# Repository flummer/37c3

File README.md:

# 37c3 NFC Badge by Thomas Flummer

This is a simple badge, to play a little with NFC using the NXP NTAG I2C Plus chip. There is a PCB antenna coil for the RF interface (can eg. be used for communication with an NFC enabled phone), and there is a StemmaQT/Qwiic compatible connector for I2C communication, often found on many development boards or more advanced badges.

The onboard memory on the NTAG I2C Plus chip is 1K and can hold different data. The badges are preformated for NDEF records and there is a link record on there that includes a link to this repository, but you can change the content, eg. with the NXP TagWriter app for Android or iOS. Be aware that iOS needs the memory to be formatted as NDEF.

You can protect different sections and it is also possible via registers to protect write access to either RF/I2C or BOTH.

**WARNING** If you block access to both interfaces, you will **NOT** be able to change the content on the badge any more.

This badge is heavily inspired with pretty much all the electronics copied from the [BornHack 2023 badge](https://github.com/bornhack/badge2023/) with almosts the same features, though a little bit less memory (the BornHack 2023 version has 2K).

## Designed in KiCad v7

To open the project, you will need to install a recent release version or one of the nightly builds, KiCad v5 or v6 won't open this design.

Main Component:

- [NXP NT3H2111W0FHKH - NTAG I2C plus 1K, NFC Forum Type 2 Tag with I2C interface](https://www.nxp.com/part/NT3H2111W0FHK#/)
    - [datasheet](https://www.nxp.com/docs/en/data-sheet/NT3H2111_2211.pdf)

## License

The hardware design of the `main` branch of this repository is released under the following license:

* the "Creative Commons Attribution-ShareAlike 4.0 International License"
  (CC BY-SA 4.0) full text of this license is included in the LICENSE file
  and a copy can also be found at
  [http://creativecommons.org/licenses/by-sa/4.0/](http://creativecommons.org/licenses/by-sa/4.0/)

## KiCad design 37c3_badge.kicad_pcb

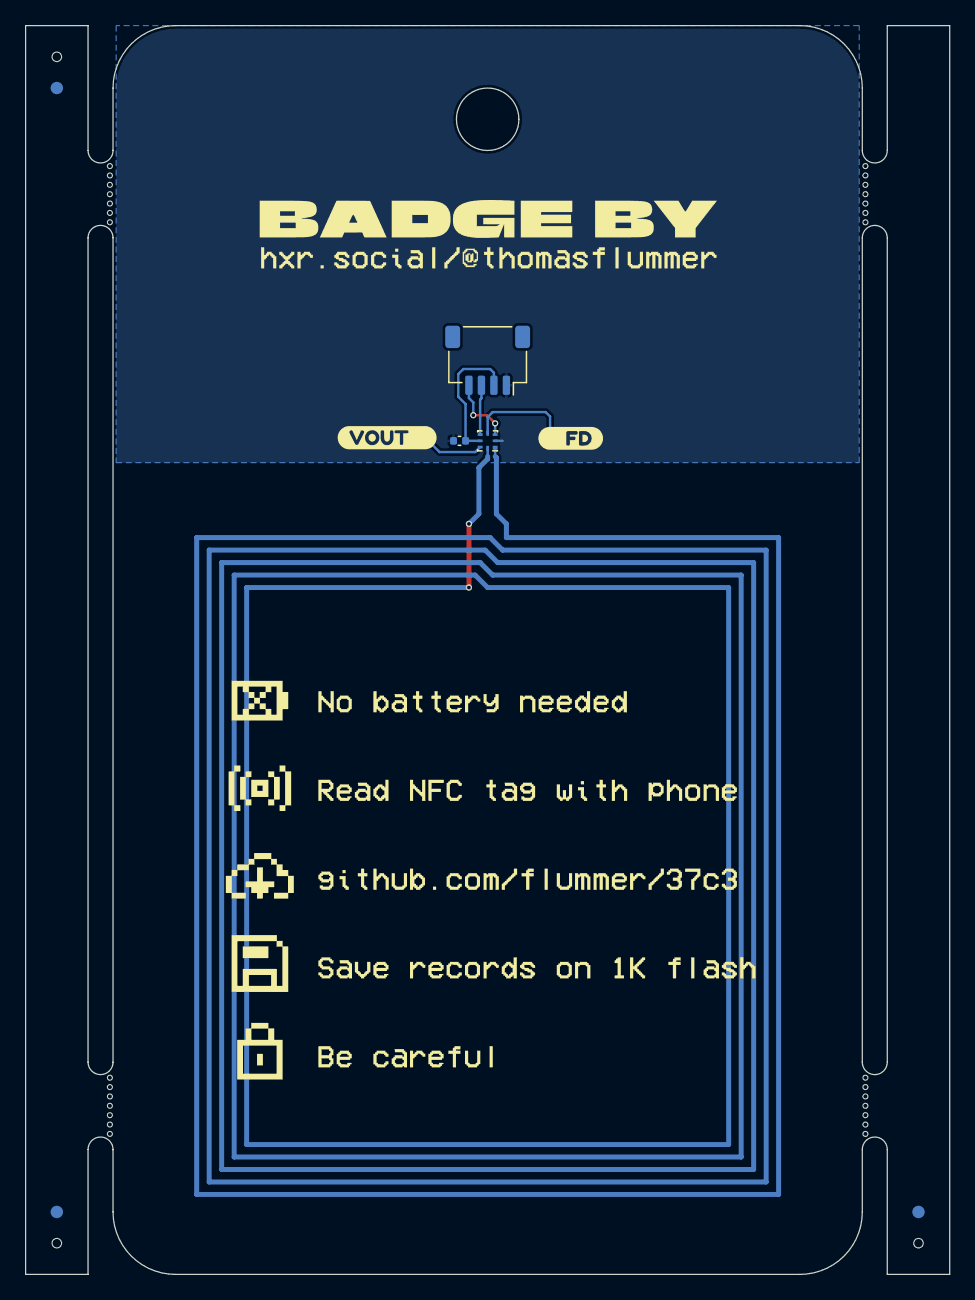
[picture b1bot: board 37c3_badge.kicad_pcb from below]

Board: 2 copper layers, 74.0 x 100.0 mm, 7 parts (7 on the bottom side), 7 nets.

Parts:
C1: 100nF; C_0402_1005Metric
J1: LCSC C7430446; JST_SH_SM04B-SRSS-TB_1x04-1MP_P1.00mm_Horizontal
TP1: VOUT; TestPoint_Pad_D1.0mm
TP2: FieldDetect; TestPoint_Pad_D1.0mm
U1: NT3H2111; NXP-XQFN-8-1.6x1.6mm
kibuzzard-6575C5F7: G***; kibuzzard-6575C5F7
kibuzzard-6575C613: G***; kibuzzard-6575C613

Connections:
/COIL: U1.1 (LA), U1.8 (LB)
/SCL: J1.4, U1.3 (SCL)
/SDA: J1.3, U1.5 (SDA)
GND: C1.2, J1.1, U1.2 (VSS)
unnamed: TP2.1, U1.4 (FD)
unnamed: TP1.1, U1.7 (Vout)
VCC: C1.1, J1.2, U1.6 (VCC)
